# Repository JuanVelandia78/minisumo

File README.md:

<h1 align="center">CAR-LOSS · Minisumo teleoperado con ROS2</h1>

<p align="center">
  Robot minisumo con <b>ESP32</b> que se maneja con un <b>guante inercial</b> o desde una <b>consola web 3D</b>, integrado con <b>ROS2</b>.<br>
  Filtrado digital en el microcontrolador, <b>filtros de Kalman</b> en el PC, control de rumbo con giroscopio y navegación a coordenadas del dojo.
</p>

<p align="center">
  <a href="INFORME.md"><b>Informe técnico</b></a> ·
  <a href="docs/Manual_de_usuario_CAR-LOSS.pdf"><b>Manual de usuario (PDF)</b></a> ·
  <a href="#puesta-en-marcha"><b>Puesta en marcha</b></a>
</p>

---

## Qué hace

- **Robot (ESP32 + PCB propia):**
  - Lee la IMU, los encoders de cuadratura y la batería a **200 Hz**.
  - Filtra en el microcontrolador: **IIR Butterworth** para la IMU y **media móvil** para las ruedas.
  - Controla cada rueda con un **PI con prealimentación** y **mantiene el rumbo** con el giroscopio. Tras un empujón de +27° vuelve a su rumbo en ≈0,3 s.
- **Guante (ESP32 + MPU-6050):** estima la inclinación de la mano con un **filtro complementario** y la envía como orden de movimiento.
- **ROS2:**
  - Puente UDP con el robot, cinemática diferencial y **tres filtros de Kalman**.
  - **Ir a un punto** con un clic en el dojo, registro de datos y RViz2.
- **Consola web:**
  - Robot 3D del CAD sobre el dojo, telemetría y gráficas crudo frente a Kalman.
  - Ajuste de ganancias en vivo, manejo manual y parada de emergencia.
  - Funciona en el PC o en el celular, sin internet.

## Arquitectura

```mermaid
flowchart LR
    G["Guante<br/>ESP32 + MPU-6050"] -- "UDP 8890" --> GT[glove_teleop]
    GT -- /cmd_vel --> DK[diff_kinematics]
    GO[goto_controller] -- /cmd_vel_auto --> DK
    DK -- /wheel_cmd --> RB[robot_bridge]
    RB <-- "UDP 8888 / 8889" --> R["Robot<br/>ESP32"]
    RB -- "/imu/raw · /wheels/speed · /odom" --> KF[kalman_filter]
    RB --> PS[panel_server]
    KF --> PS
    PS -- "/goal · /estop · /robot_cmd" --> RB
    PS <-- WebSocket --> W(["Navegador"])
```

| Nodo | Función |
|---|---|
| `robot_bridge` | Encuentra el robot por su anuncio UDP, le envía la velocidad de cada rueda y publica la telemetría. Atiende la parada de emergencia |
| `glove_teleop` | Inclinación de la mano → `/cmd_vel` |
| `diff_kinematics` | (v, ω) → velocidad de cada rueda. Da prioridad al control automático |
| `kalman_filter` | Kalman de la IMU, de las ruedas [ω, α] y de los ángulos de la mano [θ, sesgo] |
| `goto_controller` | Lleva el robot a una coordenada (x, y) del dojo |
| `panel_server` | Consola web: HTTP + WebSocket con la biblioteca estándar de Python, sin rosbridge |
| `data_logger` · `routines` · `visualizer` · `signal_plotter` | CSV, rutinas de prueba, RViz2 y gráficas de matplotlib |

## Estructura del repositorio

```
firmware/
  robot_esp32/     Firmware del robot (ESP-IDF 5.3.1, FreeRTOS): control a 200 Hz, filtros, UDP
  guante/          Firmware del guante: complementario + Butterworth, UDP
  robot/           Primera versión del robot (ESP32-C3), histórica
ros2/minisumo_ros/ Paquete ROS2: nodos, launch, consola web (web/) y modelo 3D (meshes/)
pcb/               PCB v11 en KiCad
herramientas/      cad2rviz.py (STL de SolidWorks → ROS) y figuras_informe.py
docs/              Manual de usuario (PDF), imágenes y diagrama de cableado
INFORME.md         Informe técnico (procesamiento de señales y comunicaciones)
```

## Hardware

| Bloque | Componente |
|---|---|
| Robot | ESP32 DevKit V1 · PCB v11 de una cara · DRV8833 · INA219 · MPU-6050 |
| Motores | 2 motorreductores ≈100:1 con encoder magnético (2771 cuentas/vuelta) |
| Geometría | ruedas de 30 mm (radio efectivo 16,2 mm) · 79 mm entre ruedas |
| Batería | 2S Li-ion (7,4–8,4 V) |
| Guante | ESP32 DevKit + MPU-6050 |

**Pines del robot (PCB v11):**

| Función | Pines |
|---|---|
| I²C | SDA 17 · SCL 16 |
| Motor izquierdo | AIN1 33, AIN2 32 |
| Motor derecho | BIN1 14, BIN2 13 |
| Encoders | izquierdo 18/19 · derecho 21/22 |
| Otros | STBY 26 · LED 2 |

## Puesta en marcha

### 1. Red WiFi

El robot, el guante y el PC deben estar en la **misma red de 2,4 GHz**: la ESP32 no ve redes de 5 GHz. Crea tus credenciales a partir de la plantilla:

```bash
cp firmware/robot_esp32/main/wifi_secrets.example.h firmware/robot_esp32/main/wifi_secrets.h
cp firmware/guante/main/wifi_secrets.example.h      firmware/guante/main/wifi_secrets.h
```

`wifi_secrets.h` está en `.gitignore`.

### 2. Firmware (ESP-IDF 5.3.1)

```bash
cd firmware/robot_esp32      # o firmware/guante
idf.py build flash monitor
```

- **Robot:** retira el MPU-6050 antes de flashear; con el MPU puesto la placa no entra en modo de carga.
- **Guante:** mantén **BOOT** presionado mientras carga.
- **Al encender cualquiera de los dos, déjalo quieto ≈2 s:** está calibrando el giroscopio.

### 3. ROS2

```bash
mkdir -p ~/ros2_ws/src && cp -r ros2/minisumo_ros ~/ros2_ws/src/
cd ~/ros2_ws && colcon build --packages-select minisumo_ros && source install/setup.bash
ros2 launch minisumo_ros visualizacion.launch.py guante:=true rviz:=false
```

La consola queda en `http://<IP del PC con ROS2>:8080`.

### 4. Máquina virtual (VirtualBox)

- **En modo puente (adaptador WiFi):** todo funciona directo.
- **Si el hotspot no le da IP a la VM** (algunos celulares bloquean el tráfico en puente): usa **NAT** con estos reenvíos de puertos:

| Nombre | Protocolo | Anfitrión | Invitado |
|---|---|---|---|
| robot | UDP | 8889 | 8889 |
| guante | UDP | 8890 | 8890 |
| panel | TCP | 8081 | 8080 |

En NAT, la consola se abre en `http://localhost:8081` desde Windows.

## Uso rápido

| Acción | Cómo |
|---|---|
| Manejar con el guante | Inclina la mano: adelante o atrás para avanzar, de lado para girar. **BOOT** fija el cero |
| Manejar desde la consola | **Control → Manejo manual**: pad táctil o W A S D |
| Ir a un punto | Robot en el centro del dojo mirando a +x → **Reiniciar odometría** → **Ir a punto** (G) → clic en el dojo |
| Parar | Botón **PARAR** o la barra espaciadora. **Liberar** para seguir |
| Ver los filtros | **Señales y Kalman**: crudo frente a Kalman, con σ y % de reducción |

Para usuarios no técnicos: [**Manual de usuario (PDF)**](docs/Manual_de_usuario_CAR-LOSS.pdf).

## Protocolo UDP (resumen)

| Dirección | Puerto | Contenido |
|---|---|---|
| Robot → PC (broadcast) | 8889 | `MINISUMO,<ip>,8888` cada 1 s |
| PC → robot | 8888 | `W,wl,wr` · `S` · `G,…` · `F,…` · `Y,…` · `R` · `C` · `T` · `H` |
| Robot → PC | (al emisor) | `H,…` cabecera de 33 columnas · `D,…` telemetría a 200 Hz, 6 líneas por paquete |
| Guante → PC | 8890 | `GL,t,pitch,roll,…` a 50 Hz (unicast después de recibir `GLP`) |

El detalle está en el [informe](INFORME.md#6-comunicaciones).

## Documentación

- [**INFORME.md**](INFORME.md): procesamiento digital de señales (IIR, media móvil, complementario, Kalman), control, comunicaciones y ROS2, con resultados medidos.
- [**Manual de usuario**](docs/Manual_de_usuario_CAR-LOSS.pdf): guía visual paso a paso.
- [`docs/cableado.html`](docs/cableado.html): diagrama de cableado.
- [`DESIGN.md`](DESIGN.md): sistema de diseño de la consola.

## Licencia

MIT

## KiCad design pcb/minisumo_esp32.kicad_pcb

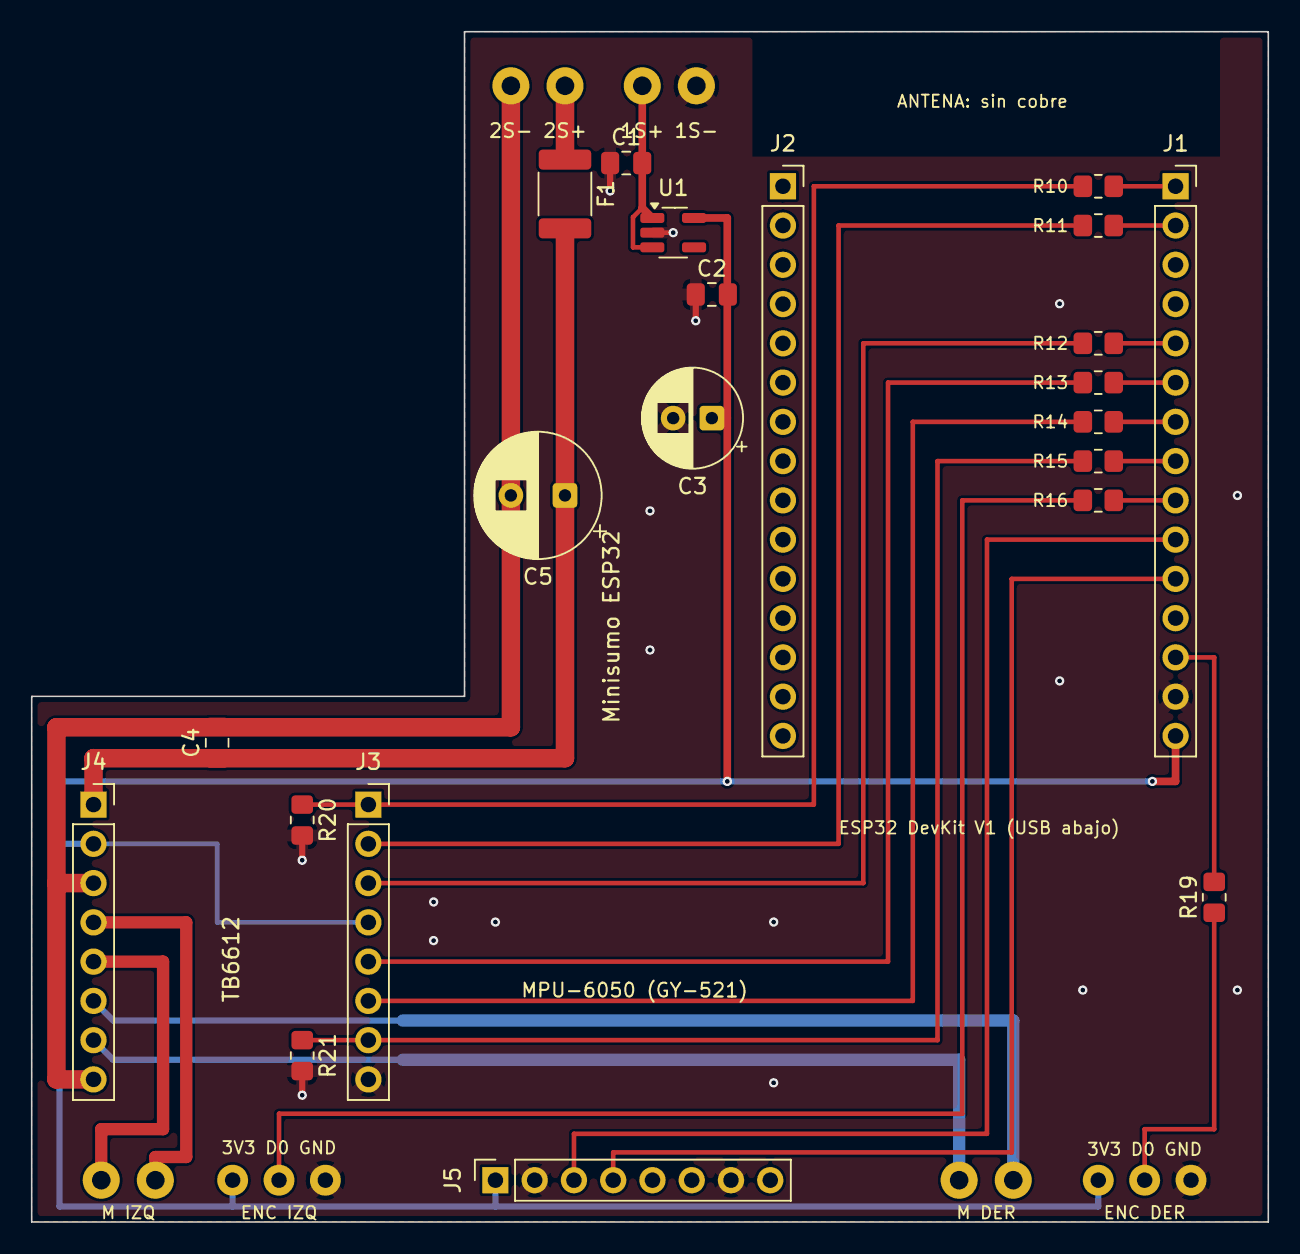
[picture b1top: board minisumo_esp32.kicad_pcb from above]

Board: 2 copper layers, 80.0 x 77.0 mm, 36 parts (0 on the bottom side), 28 nets.

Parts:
BAT1N: 1S -
BAT1P: 1S +
BAT2N: 2S -
BAT2P: 2S +
C1, C2: 1uF; C_0805_2012Metric_Pad1.18x1.45mm_HandSolder
C3: 100uF 10V; CP_Radial_D6.3mm_P2.50mm
C4: 100nF; C_0805_2012Metric_Pad1.18x1.45mm_HandSolder
C5: 470uF 16V; CP_Radial_D8.0mm_P3.50mm
ELD: Enc izq D0
ELG: Enc izq GND
ELV: Enc izq 3V3
ERD: Enc der D0
ERG: Enc der GND
ERV: Enc der 3V3
F1: PTC 1A; Fuse_1812_4532Metric_Pad1.30x3.40mm_HandSolder
J1: ESP32 fila derecha; PinSocket_1x15_P2.54mm_Vertical
J2: ESP32 fila izquierda (soporte); PinSocket_1x15_P2.54mm_Vertical
J3: TB6612 control; PinSocket_1x08_P2.54mm_Vertical
J4: TB6612 potencia; PinSocket_1x08_P2.54mm_Vertical
J5: MPU-6050 GY-521; PinSocket_1x08_P2.54mm_Vertical
MA1, MA2: Motor izq.
MB1, MB2: Motor der.
R10, R11, R12, R13, R14, R15: 220; R_0805_2012Metric_Pad1.20x1.40mm_HandSolder
R16, R19: 1k; R_0805_2012Metric_Pad1.20x1.40mm_HandSolder
R20, R21: 10k; R_0805_2012Metric_Pad1.20x1.40mm_HandSolder
U1: XC6220B331MR; SOT-23-5_HandSoldering

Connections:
+3V3: C2.2, C3.1, ELV.1, ERV.1, J1.15, J3.4, J4.2, J5.1, U1.5
AIN1: J3.3, R12.1
AIN1_ESP: J1.5, R12.2
AIN2: J3.2, R11.1
AIN2_ESP: J1.2, R11.2
AO1: J4.4, MA2.1
AO2: J4.5, MA1.1
BIN1: J3.5, R13.1
BIN1_ESP: J1.6, R13.2
BIN2: J3.6, R14.1
BIN2_ESP: J1.7, R14.2
BO1: J4.7, MB1.1
BO2: J4.6, MB2.1
ENCL: ELD.1, R16.1
ENCL_ESP: J1.9, R16.2
ENCR: ERD.1, R19.1
ENCR_ESP: J1.13, R19.2
GND: BAT1N.1, C1.1, C2.1, C3.2, ELG.1, ERG.1, J1.14, J3.8, J5.2, J5.7, R20.2, R21.2, U1.2
GND_MOT: BAT2N.1, C4.2, C5.2, J4.3, J4.8
PWMA: J3.1, R10.1, R20.1
PWMA_ESP: J1.1, R10.2
PWMB: J3.7, R15.1, R21.1
PWMB_ESP: J1.8, R15.2
SCL: J1.10, J5.3
SDA: J1.11, J5.4
VBAT1: BAT1P.1, C1.2, U1.1, U1.3
VBAT2: BAT2P.1, F1.1
VM: C4.1, C5.1, F1.2, J4.1

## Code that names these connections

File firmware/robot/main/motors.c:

#include "motors.h"
#include "config.h"
#include "driver/ledc.h"
#include "driver/gpio.h"

#define CH_L LEDC_CHANNEL_0
#define CH_R LEDC_CHANNEL_1
#define DUTY_FULL ((1 << PWM_RES_BITS) - 1)

void motors_init(void)
{
    gpio_config_t io = {
        .pin_bit_mask = (1ULL << PIN_AIN1) | (1ULL << PIN_AIN2) | (1ULL << PIN_BIN1) | (1ULL << PIN_BIN2),
        .mode = GPIO_MODE_OUTPUT,
    };
    gpio_config(&io);
    gpio_set_level(PIN_AIN1, 0);
    gpio_set_level(PIN_AIN2, 0);
    gpio_set_level(PIN_BIN1, 0);
    gpio_set_level(PIN_BIN2, 0);

    ledc_timer_config_t t = {
        .speed_mode = LEDC_LOW_SPEED_MODE,
        .duty_resolution = PWM_RES_BITS,
        .timer_num = LEDC_TIMER_0,
        .freq_hz = PWM_FREQ_HZ,
        .clk_cfg = LEDC_AUTO_CLK,
    };
    ESP_ERROR_CHECK(ledc_timer_config(&t));

    ledc_channel_config_t c = {
        .speed_mode = LEDC_LOW_SPEED_MODE,
        .timer_sel = LEDC_TIMER_0,
        .duty = 0,
        .hpoint = 0,
        .flags.output_invert = PWM_OUTPUT_INVERT,   // el 6N137 vuelve a invertirla
    };
    c.gpio_num = PIN_PWMA;
    c.channel = CH_L;
    ESP_ERROR_CHECK(ledc_channel_config(&c));
    c.gpio_num = PIN_PWMB;
    c.channel = CH_R;
    ESP_ERROR_CHECK(ledc_channel_config(&c));
}

static float clampf(float x, float lim)
{
    return x > lim ? lim : (x < -lim ? -lim : x);
}

static void set_one(ledc_channel_t ch, int in1, int in2, float duty)
{
    if (duty > 0.0f) {
        gpio_set_level(in1, 1);
        gpio_set_level(in2, 0);
    } else if (duty < 0.0f) {
        gpio_set_level(in1, 0);
        gpio_set_level(in2, 1);
        duty = -duty;
    } else {
        gpio_set_level(in1, 0);                 // libre (stop)
        gpio_set_level(in2, 0);
    }
    ledc_set_duty(LEDC_LOW_SPEED_MODE, ch, (uint32_t)(duty * DUTY_FULL));
    ledc_update_duty(LEDC_LOW_SPEED_MODE, ch);
}

void motors_set(float duty_l, float duty_r, float *applied_l, float *applied_r)
{
    duty_l = clampf(duty_l, PWM_MAX);
    duty_r = clampf(duty_r, PWM_MAX);
    set_one(CH_L, PIN_AIN1, PIN_AIN2, MOTOR_L_INVERT ? -duty_l : duty_l);
    set_one(CH_R, PIN_BIN1, PIN_BIN2, MOTOR_R_INVERT ? -duty_r : duty_r);
    if (applied_l) *applied_l = duty_l;
    if (applied_r) *applied_r = duty_r;
}

void motors_stop(void)
{
    motors_set(0.0f, 0.0f, NULL, NULL);
}
